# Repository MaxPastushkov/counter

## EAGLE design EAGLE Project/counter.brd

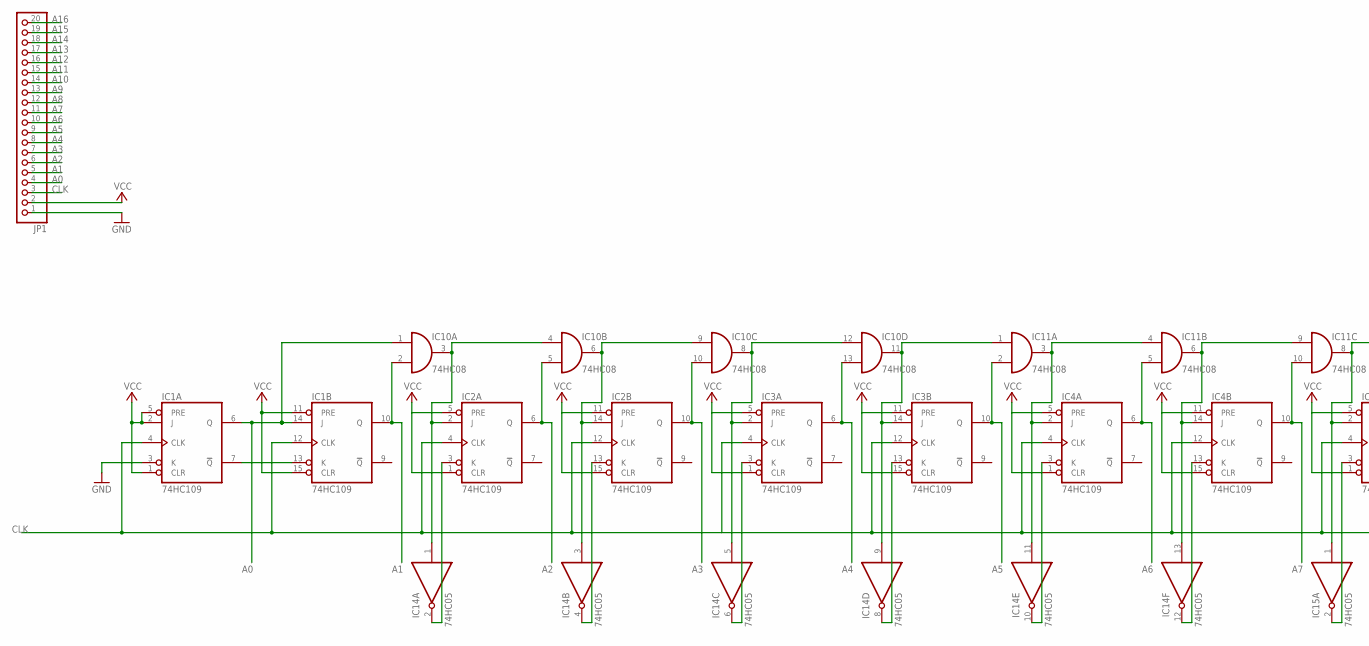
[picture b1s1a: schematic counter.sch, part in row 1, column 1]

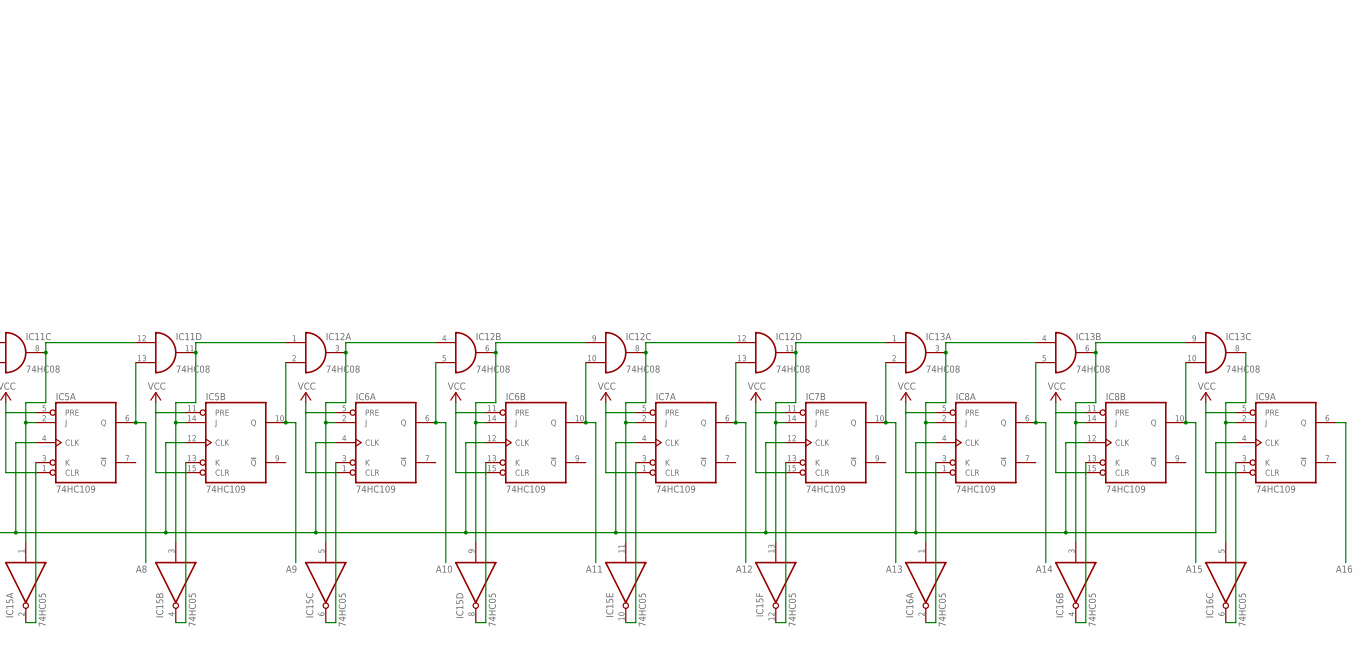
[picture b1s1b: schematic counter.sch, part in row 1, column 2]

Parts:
IC1, IC2, IC3, IC4, IC5, IC6, IC7, IC8, IC9: 74HC109; DIL16
IC10, IC11, IC12, IC13: 74HC08; DIL14
IC14, IC15, IC16: 74HC05; DIL14
JP1: PINHD-1X20; 1X20

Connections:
A0: IC1.6 (Q), IC1.14 (J), IC10.1 (I0), JP1.4
A1: IC1.10 (Q), IC10.2 (I1), JP1.5
A2: IC2.6 (Q), IC10.5 (I1), JP1.6
A3: IC2.10 (Q), IC10.10 (I1), JP1.7
A4: IC3.6 (Q), IC10.13 (I1), JP1.8
A5: IC3.10 (Q), IC11.2 (I1), JP1.9
A6: IC4.6 (Q), IC11.5 (I1), JP1.10
A7: IC4.10 (Q), IC11.10 (I1), JP1.11
A8: IC5.6 (Q), IC11.13 (I1), JP1.12
A9: IC5.10 (Q), IC12.2 (I1), JP1.13
A10: IC6.6 (Q), IC12.5 (I1), JP1.14
A11: IC6.10 (Q), IC12.10 (I1), JP1.15
A12: IC7.6 (Q), IC12.13 (I1), JP1.16
A13: IC7.10 (Q), IC13.2 (I1), JP1.17
A14: IC8.6 (Q), IC13.5 (I1), JP1.18
A15: IC8.10 (Q), IC13.10 (I1), JP1.19
A16: IC9.6 (Q), JP1.20
CLK: IC1.4 (CLK), IC1.12 (CLK), IC2.4 (CLK), IC2.12 (CLK), IC3.4 (CLK), IC3.12 (CLK), IC4.4 (CLK), IC4.12 (CLK), IC5.4 (CLK), IC5.12 (CLK), IC6.4 (CLK), IC6.12 (CLK), IC7.4 (CLK), IC7.12 (CLK), IC8.4 (CLK), IC8.12 (CLK), IC9.4 (CLK), JP1.3
GND: IC1.3 (K), IC1.8 (GND), IC2.8 (GND), IC3.8 (GND), IC4.8 (GND), IC5.8 (GND), IC6.8 (GND), IC7.8 (GND), IC8.8 (GND), IC9.8 (GND), IC10.7 (GND), IC11.7 (GND), IC12.7 (GND), IC13.7 (GND), IC14.7 (GND), IC15.7 (GND), IC16.7 (GND), JP1.1
unnamed: IC1.7 (!Q), IC1.13 (K)
unnamed: IC2.3 (K), IC14.2 (O)
unnamed: IC2.13 (K), IC14.4 (O)
unnamed: IC2.14 (J), IC10.6 (O), IC10.9 (I0), IC14.3 (I)
unnamed: IC3.2 (J), IC10.8 (O), IC10.12 (I0), IC14.5 (I)
unnamed: IC2.2 (J), IC10.3 (O), IC10.4 (I0), IC14.1 (I)
unnamed: IC3.3 (K), IC14.6 (O)
unnamed: IC3.13 (K), IC14.8 (O)
unnamed: IC3.14 (J), IC10.11 (O), IC11.1 (I0), IC14.9 (I)
unnamed: IC4.3 (K), IC14.10 (O)
unnamed: IC4.14 (J), IC11.6 (O), IC11.9 (I0), IC14.13 (I)
unnamed: IC5.2 (J), IC11.8 (O), IC11.12 (I0), IC15.1 (I)
unnamed: IC4.13 (K), IC14.12 (O)
unnamed: IC5.3 (K), IC15.2 (O)
unnamed: IC5.13 (K), IC15.4 (O)
unnamed: IC6.3 (K), IC15.6 (O)
unnamed: IC6.13 (K), IC15.8 (O)
unnamed: IC7.3 (K), IC15.10 (O)
unnamed: IC7.13 (K), IC15.12 (O)
unnamed: IC8.3 (K), IC16.2 (O)
unnamed: IC8.13 (K), IC16.4 (O)
unnamed: IC9.3 (K), IC16.6 (O)
unnamed: IC4.2 (J), IC11.3 (O), IC11.4 (I0), IC14.11 (I)
unnamed: IC5.14 (J), IC11.11 (O), IC12.1 (I0), IC15.3 (I)
unnamed: IC6.2 (J), IC12.3 (O), IC12.4 (I0), IC15.5 (I)
unnamed: IC6.14 (J), IC12.6 (O), IC12.9 (I0), IC15.9 (I)
unnamed: IC7.2 (J), IC12.8 (O), IC12.12 (I0), IC15.11 (I)
unnamed: IC7.14 (J), IC12.11 (O), IC13.1 (I0), IC15.13 (I)
unnamed: IC8.2 (J), IC13.3 (O), IC13.4 (I0), IC16.1 (I)
unnamed: IC8.14 (J), IC13.6 (O), IC13.9 (I0), IC16.3 (I)
unnamed: IC9.2 (J), IC13.8 (O), IC16.5 (I)
VCC: IC1.1 (CLR), IC1.2 (J), IC1.5 (PRE), IC1.11 (PRE), IC1.15 (CLR), IC1.16 (VCC), IC2.1 (CLR), IC2.5 (PRE), IC2.11 (PRE), IC2.15 (CLR), IC2.16 (VCC), IC3.1 (CLR), IC3.5 (PRE), IC3.11 (PRE), IC3.15 (CLR), IC3.16 (VCC), IC4.1 (CLR), IC4.5 (PRE), IC4.11 (PRE), IC4.15 (CLR), IC4.16 (VCC), IC5.1 (CLR), IC5.5 (PRE), IC5.11 (PRE), IC5.15 (CLR), IC5.16 (VCC), IC6.1 (CLR), IC6.5 (PRE), IC6.11 (PRE), IC6.15 (CLR), IC6.16 (VCC), IC7.1 (CLR), IC7.5 (PRE), IC7.11 (PRE), IC7.15 (CLR), IC7.16 (VCC), IC8.1 (CLR), IC8.5 (PRE), IC8.11 (PRE), IC8.15 (CLR), IC8.16 (VCC), IC9.1 (CLR), IC9.5 (PRE), IC9.16 (VCC), IC10.14 (VCC), IC11.14 (VCC), IC12.14 (VCC), IC13.14 (VCC), IC14.14 (VCC), IC15.14 (VCC), IC16.14 (VCC), JP1.2

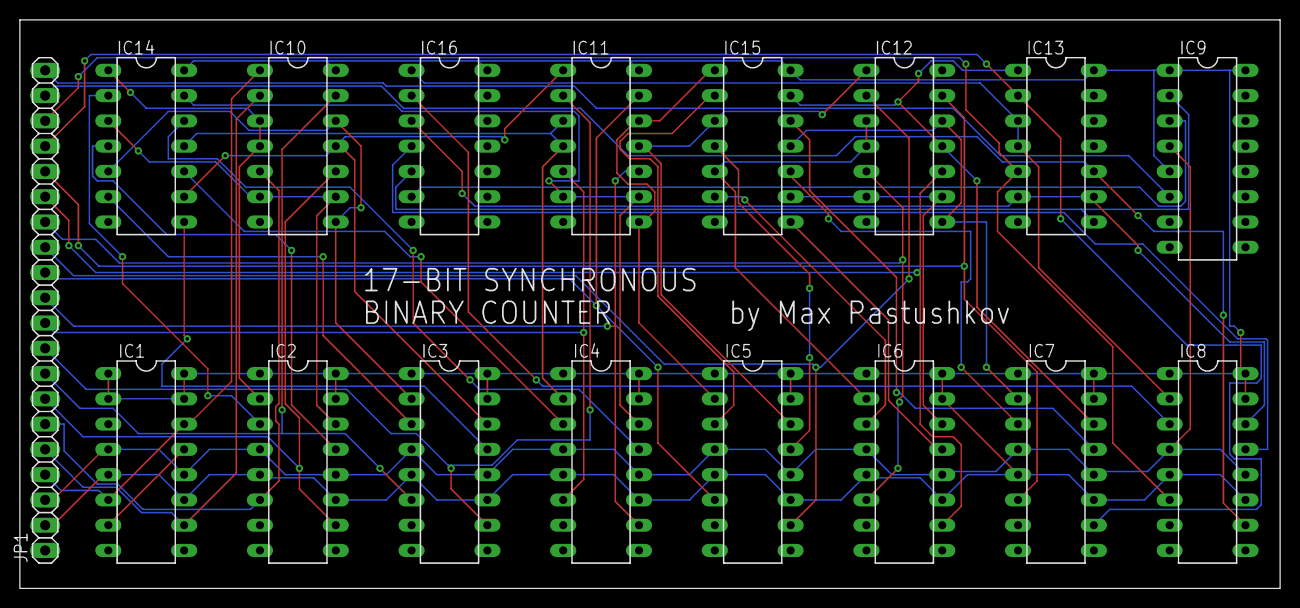
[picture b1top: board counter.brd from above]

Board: 2 copper layers, 126.7 x 57.1 mm, 17 parts (0 on the bottom side), 51 nets.

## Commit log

2020-10-16 add all files
